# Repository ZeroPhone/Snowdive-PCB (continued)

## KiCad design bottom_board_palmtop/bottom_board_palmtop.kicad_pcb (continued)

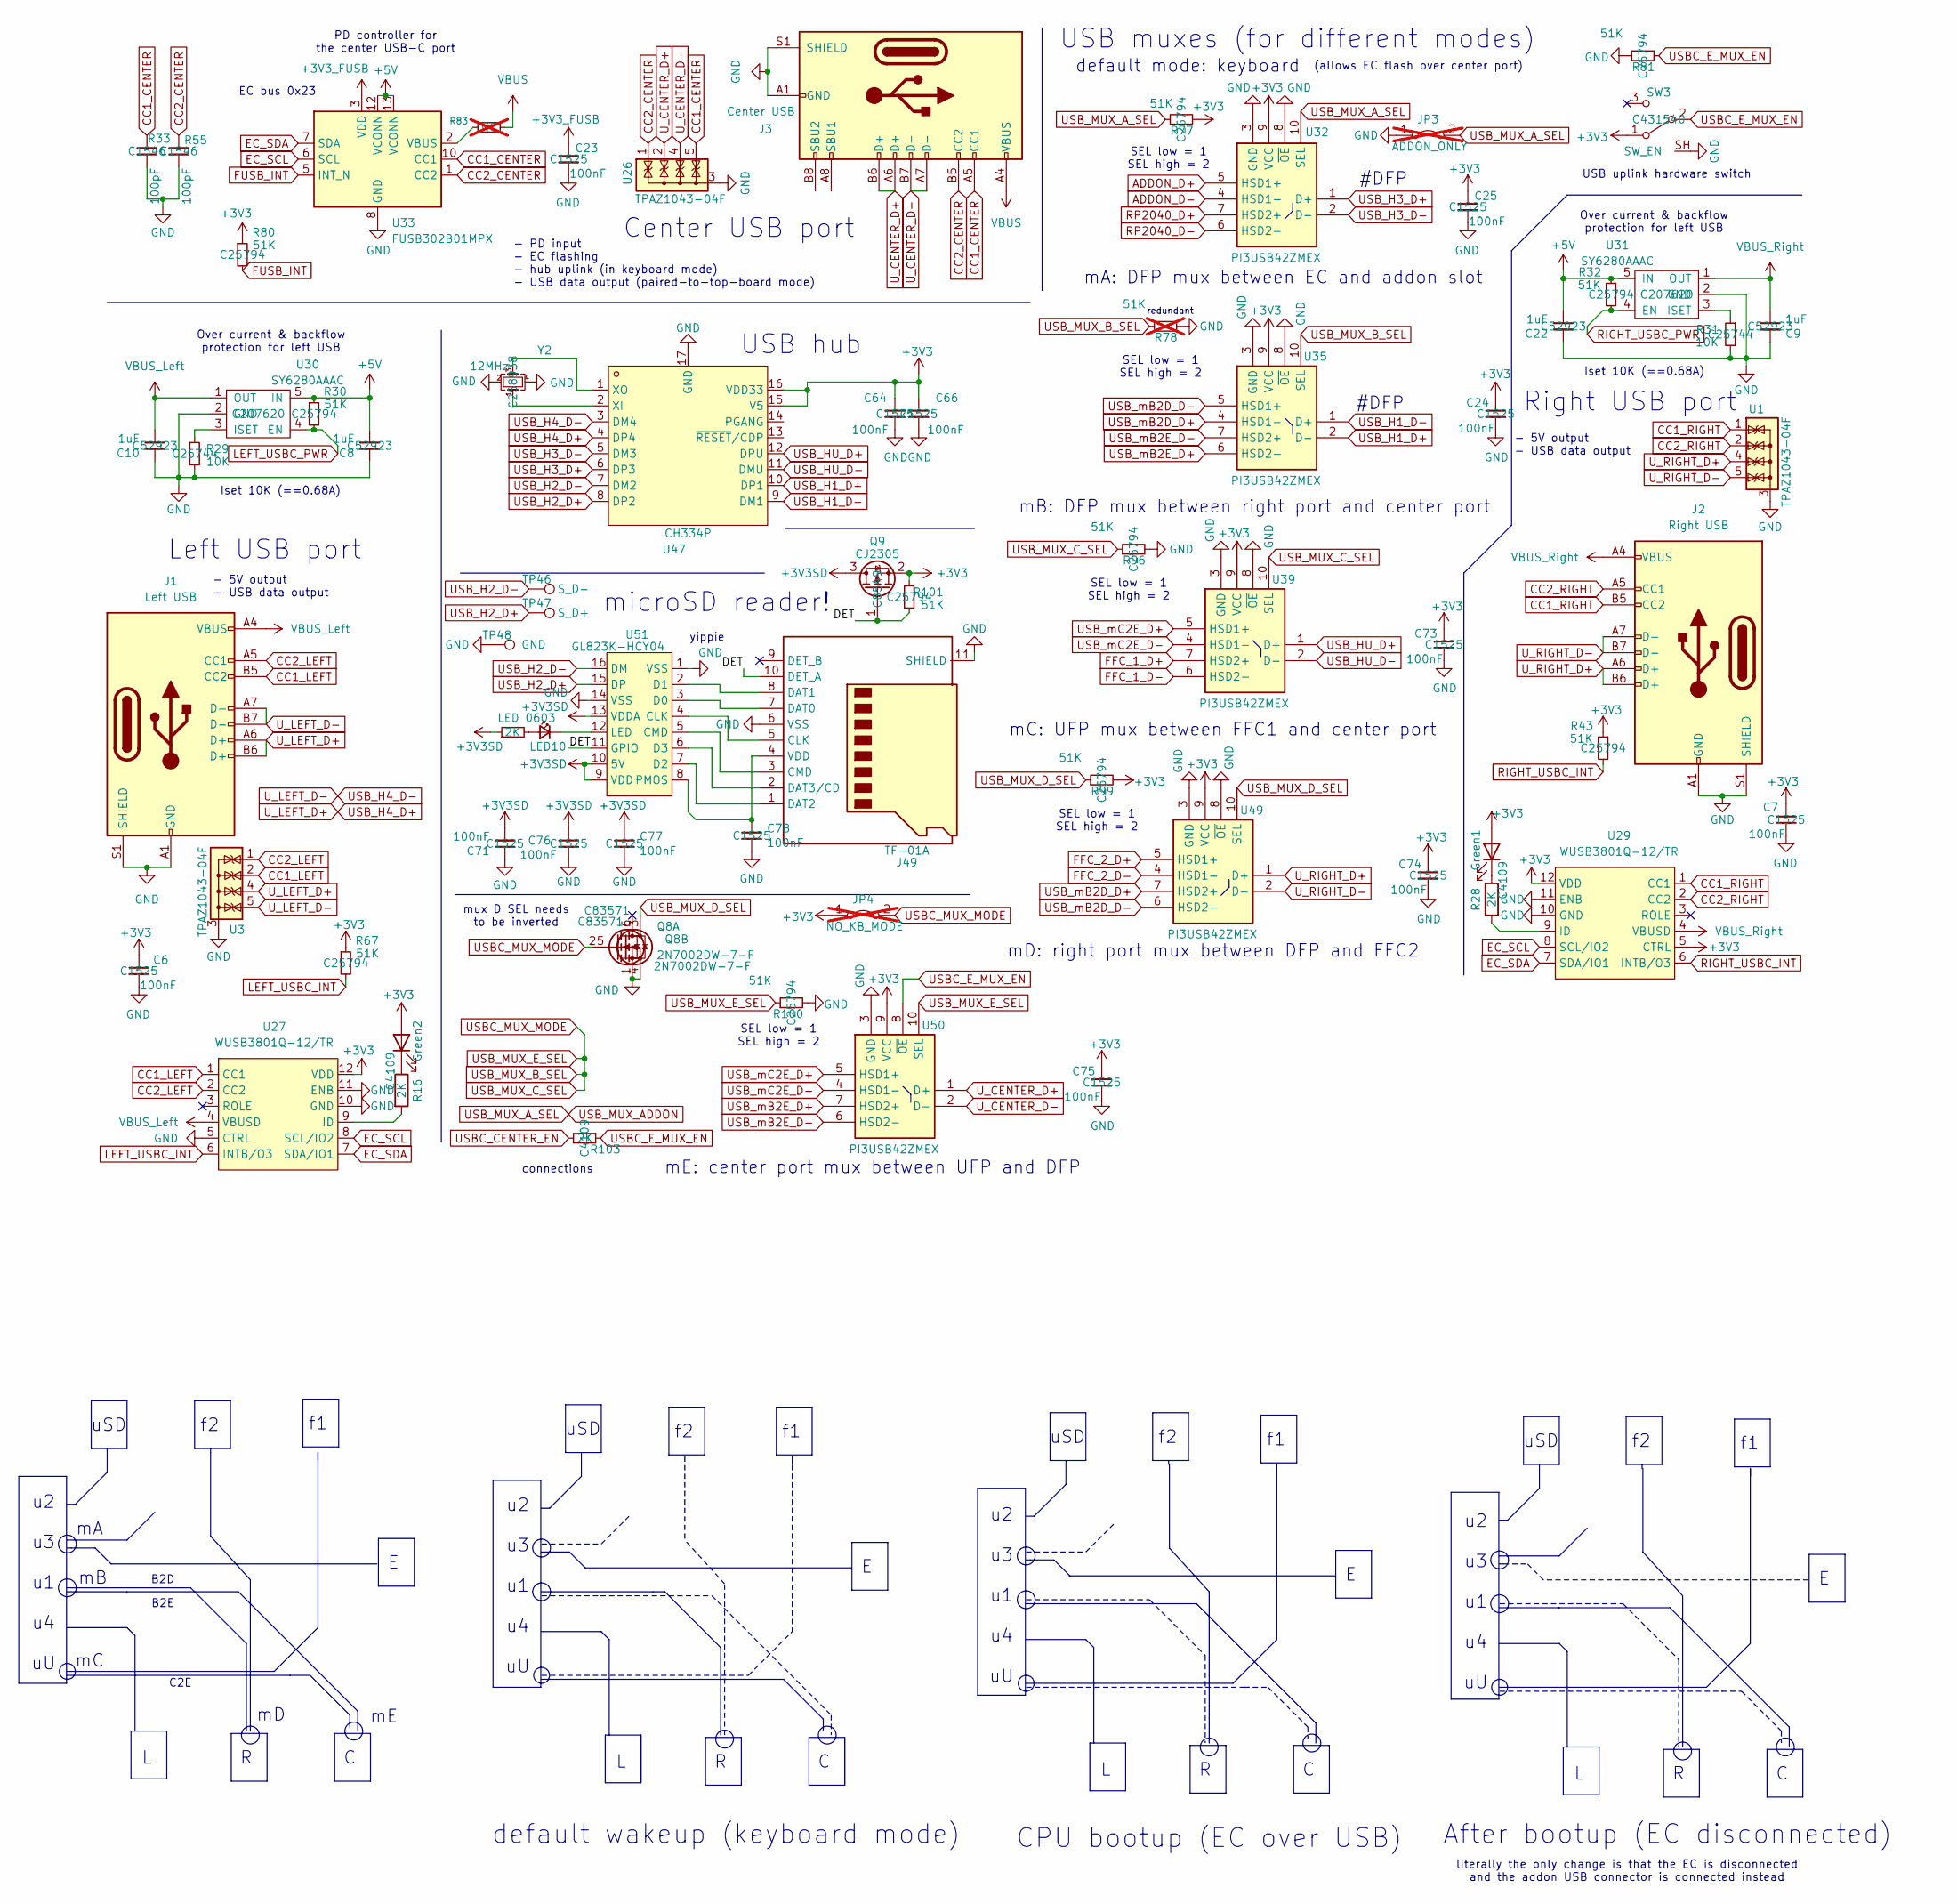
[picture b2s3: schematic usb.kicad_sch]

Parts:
C6, C7, C23, C24, C25, C64, C66, C71, C73, C74, C75, C76, C77, C78: 100nF; C_0402_1005Metric; LCSC Part C1525
C8, C9, C10, C22: 1uF; C_0402_1005Metric; LCSC Part C52923
Green1, Green2: LED 0603 Green; LED_0603_1608Metric
J1: Left USB; USB-C-TH_MC-710; LCSC Part C3039315
J2: Right USB; USB-C-TH_MC-710; LCSC Part C3039315
J3: Center USB; USB_C_Receptacle_HRO_TYPE-C-31-M-12; LCSC Part C165948
J49: TF-01A; microSD-Receptacle-SelfEject; LCSC Part C91145
JP3: ADDON_ONLY; SolderJumper-2_smol_Open; not fitted
JP4: NO_KB_MODE; SolderJumper-2_smol_Open; not fitted
LED10: LED 0603; LED_0603_1608Metric; LCSC Part C2977076
Q8: 2N7002DW-7-F; SOT-363_SC-70-6; LCSC Part C83571
Q9: CJ2305; SOT-23; LCSC Part C8549
R16, R28, R102, R103: 2K; R_0402_1005Metric; LCSC Part C4109
R29, R31: 10K; R_0402_1005Metric; LCSC Part C25744
R30, R32, R43, R67, R77, R80, R81, R96, R99, R100, R101: 51K; R_0402_1005Metric; LCSC Part C25794
R33, R55: 100pF; R_0402_1005Metric; LCSC Part C1546
R78: 51K; R_0402_1005Metric; LCSC Part C25794; not fitted
R83: NC; R_0402_1005Metric; not fitted
SW3: SW_EN; SW_SPDT_PCM12_SH; LCSC Part C431540
TP46: S_D-; TestPoint_Pad_0.6x0.6mm
TP47: S_D+; TestPoint_Pad_0.6x0.6mm
TP48: GND; TestPoint_Pad_0.6x0.6mm
U1, U3, U26: TPAZ1043-04F; USON-10_2.5x1.0mm_P0.5mm
U27, U29: WUSB3801Q-12/TR; X2QFN-12_L1.6-W1.6-P0.40-LS1.2; LCSC Part C2931342
U30, U31: SY6280AAAC; SOT-23-5; LCSC Part C207620
U32, U35, U39, U49, U50: PI3USB42ZMEX; QFN40P140X180X55-10N; Manufacturer_Part_Number FSUSB42UMX; Mouser Part Number 512-FSUSB42UMX
U33: FUSB302B01MPX; WQFN-14-1EP_2.5x2.5mm_P0.5mm_EP1.45x1.45mm
U47: CH334P; QFN-16-1EP_3x3mm_P0.5mm_EP1.7x1.7mm; LCSC Part C5373042
U51: GL823K-HCY04; SSOP-16_3.9x4.9mm_P0.635mm; LCSC Part C284879
Y2: 12MHz; Crystal_SMD_3225-4Pin_3.2x2.5mm; LCSC Part C258938

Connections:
+3V3: C6.1, C7.1, C24.1, C25.1, C64.1, C66.1, C73.1, C74.1, C75.1, Green1.2 (A), Green2.2 (A), JP4.1 (A), Q9.2 (S), R43.1, R67.1, R77.2, R80.1, R99.2, R101.1, SW3.1 (A), U27.12 (VDD), U29.5 (CTRL), U29.12 (VDD), U32.9 (VCC), U35.9 (VCC), U39.9 (VCC), U47.15 (V5), U47.16 (VDD33), U49.9 (VCC), U50.9 (VCC); also elsewhere on the board
+3V3SD: C71.2, C76.1, C77.1, Q9.3 (D), R102.1, U51.9 (VDD), U51.10 (5V), U51.13 (VDDA)
+3V3_FUSB: C23.1, U33.3 (VDD), U33.4 (VDD); also elsewhere on the board
+5V: C8.1, C22.1, R30.1, R32.1, U30.5 (IN), U31.5 (IN), U33.12 (VCONN), U33.13 (VCONN); also elsewhere on the board
/USB/DET: J49.10 (DET_A), Q9.1 (G), R101.2, U51.11 (GPIO)
ADDON_D+: U32.5 (HSD1+); also elsewhere on the board
ADDON_D-: U32.4 (HSD1-); also elsewhere on the board
CC1_CENTER: J3.A5 (CC1), R33.2, U26.5 (IO4), U26.6 (NC), U33.10 (CC1), U33.11 (CC1)
CC1_LEFT: J1.B5 (CC2), U3.2 (IO2), U3.9 (NC), U27.1 (CC1)
CC1_RIGHT: J2.B5 (CC2), U1.1 (IO1), U1.10 (NC), U29.1 (CC1)
CC2_CENTER: J3.B5 (CC2), R55.2, U26.1 (IO1), U26.10 (NC), U33.1 (CC2), U33.14 (CC2)
CC2_LEFT: J1.A5 (CC1), U3.1 (IO1), U3.10 (NC), U27.2 (CC2)
CC2_RIGHT: J2.A5 (CC1), U1.2 (IO2), U1.9 (NC), U29.2 (CC2)
EC_SCL: U27.8 (SCL/IO2), U29.8 (SCL/IO2), U33.6 (SCL); also elsewhere on the board
EC_SDA: U27.7 (SDA/IO1), U29.7 (SDA/IO1), U33.7 (SDA); also elsewhere on the board
FFC_1_D+: U39.7 (HSD2+); also elsewhere on the board
FFC_1_D-: U39.6 (HSD2-); also elsewhere on the board
FFC_2_D+: U49.5 (HSD1+); also elsewhere on the board
FFC_2_D-: U49.4 (HSD1-); also elsewhere on the board
FUSB_INT: R80.2, U33.5 (INT_N); also elsewhere on the board
GND: C6.2, C7.2, C8.2, C9.2, C10.2, C22.2, C23.2, C24.2, C25.2, C64.2, C66.2, C71.1, C73.2, C74.2, C75.2, C76.2, C77.2, C78.2, J1.A1 (GND), J1.A12 (GND), J1.B1 (GND), J1.B12 (GND), J1.S1 (SHIELD), J2.A1 (GND), J2.A12 (GND), J2.B1 (GND), J2.B12 (GND), J2.S1 (SHIELD), J3.A1 (GND), J3.A12 (GND), J3.B1 (GND), J3.B12 (GND), J3.S1 (SHIELD), J49.6 (VSS), J49.11 (SHIELD), JP3.1 (A), Q8.1 (S), Q8.4 (S), R29.2, R31.2, R33.1, R55.1, R78.2, R81.1, R96.2, R100.2, SW3.SH, TP48.1, U1.3 (G), U1.8 (G), U3.3 (G), U3.8 (G), U26.3 (G), U26.8 (G), U27.5 (CTRL), U27.10 (GND), U27.11 (ENB), U29.10 (GND), U29.11 (ENB), U30.2 (GND), U31.2 (GND), U32.3 (GND), U32.8 (~OE), U33.8 (GND), U33.9 (GND), U33.15 (GND), U35.3 (GND), U35.8 (~OE), U39.3 (GND), U39.8 (~OE), U47.17 (GND), U49.3 (GND), U49.8 (~OE), U50.3 (GND), U51.1 (VSS), U51.14 (VSS), Y2.2, Y2.4; also elsewhere on the board
LEFT_USBC_INT: R67.2, U27.6 (INTB/O3); also elsewhere on the board
LEFT_USBC_PWR: R30.2, U30.4 (EN); also elsewhere on the board
unnamed: Green1.1 (K), R28.1
unnamed: Green2.1 (K), R16.1
unnamed: J49.5 (CLK), U51.4 (CLK)
unnamed: J49.3 (CMD), U51.5 (CMD)
unnamed: J49.7 (DAT0), U51.3 (D0)
unnamed: J49.8 (DAT1), U51.2 (D1)
unnamed: J49.1 (DAT2), U51.7 (D2)
unnamed: J49.2 (DAT3/CD), U51.6 (D3)
unnamed: C78.1, J49.4 (VDD), U51.8 (PMOS)
unnamed: LED10.2 (A), R102.2
unnamed: LED10.1 (K), U51.12 (LED)
unnamed: R16.2, U27.9 (ID)
unnamed: R28.2, U29.9 (ID)
unnamed: R29.1, U30.3 (ISET)
unnamed: R31.1, U31.3 (ISET)
unnamed: R83.1, U33.2 (VBUS)
unnamed: U47.2 (XI), Y2.1
unnamed: U47.1 (XO), Y2.3
RIGHT_USBC_INT: R43.2, U29.6 (INTB/O3); also elsewhere on the board
RIGHT_USBC_PWR: R32.2, U31.4 (EN); also elsewhere on the board
RP2040_D+: U32.7 (HSD2+); also elsewhere on the board
RP2040_D-: U32.6 (HSD2-); also elsewhere on the board
USBC_CENTER_EN: R103.2; also elsewhere on the board
USBC_E_MUX_EN: R81.2, R103.1, SW3.2 (B), U50.8 (~OE)
USBC_MUX_MODE: JP4.2 (B), Q8.2 (G), Q8.5 (G), R78.1, R96.1, R100.1, U35.10 (SEL), U39.10 (SEL), U50.10 (SEL); also elsewhere on the board
USB_H1_D+: U35.2 (D-), U47.10 (DP1)
USB_H1_D-: U35.1 (D+), U47.9 (DM1)
USB_H2_D+: TP47.1, U47.8 (DP2), U51.15 (DP)
USB_H2_D-: TP46.1, U47.7 (DM2), U51.16 (DM)
USB_H3_D+: U32.1 (D+), U47.6 (DP3)
USB_H3_D-: U32.2 (D-), U47.5 (DM3)
USB_H4_D+: J1.A6 (D+), J1.B6 (D+), U3.4 (IO3), U3.7 (NC), U47.4 (DP4)
USB_H4_D-: J1.A7 (D-), J1.B7 (D-), U3.5 (IO4), U3.6 (NC), U47.3 (DM4)
USB_HU_D+: U39.1 (D+), U47.12 (DPU)
USB_HU_D-: U39.2 (D-), U47.11 (DMU)
USB_MUX_ADDON: JP3.2 (B), R77.1, U32.10 (SEL); also elsewhere on the board
USB_MUX_D_SEL: Q8.3 (D), R99.1, U49.10 (SEL)
USB_mB2D_D+: U35.4 (HSD1-), U49.7 (HSD2+)
USB_mB2D_D-: U35.5 (HSD1+), U49.6 (HSD2-)
USB_mB2E_D+: U35.6 (HSD2-), U50.7 (HSD2+)
USB_mB2E_D-: U35.7 (HSD2+), U50.6 (HSD2-)
USB_mC2E_D+: U39.5 (HSD1+), U50.5 (HSD1+)
USB_mC2E_D-: U39.4 (HSD1-), U50.4 (HSD1-)
U_CENTER_D+: J3.A6 (D+), J3.B6 (D+), U26.2 (IO2), U26.9 (NC), U50.1 (D+)
U_CENTER_D-: J3.A7 (D-), J3.B7 (D-), U26.4 (IO3), U26.7 (NC), U50.2 (D-)
U_RIGHT_D+: J2.A6 (D+), J2.B6 (D+), U1.4 (IO3), U1.7 (NC), U49.1 (D+)
U_RIGHT_D-: J2.A7 (D-), J2.B7 (D-), U1.5 (IO4), U1.6 (NC), U49.2 (D-)
VBUS: J3.A4 (VBUS), J3.A9 (VBUS), J3.B4 (VBUS), J3.B9 (VBUS), R83.2; also elsewhere on the board
VBUS_Left: C10.1, J1.A4 (VBUS), J1.A9 (VBUS), J1.B4 (VBUS), J1.B9 (VBUS), U27.4 (VBUSD), U30.1 (OUT)
VBUS_Right: C9.1, J2.A4 (VBUS), J2.A9 (VBUS), J2.B4 (VBUS), J2.B9 (VBUS), U29.4 (VBUSD), U31.1 (OUT)

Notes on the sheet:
default wakeup (keyboard mode)
Center USB port
yippie
literally the only change is that the EC is disconnected and the addon USB connector is connected instead
u2 u3 u1 u4 uU
SEL low = 1 SEL high = 2
C2E
Iset 10K (==0.68A)
default mode: keyboard
#DFP
uSD
- 5V output - USB data output
USB uplink hardware switch
microSD reader!
EC bus 0x23
USB muxes (for different modes)
mB: DFP mux between right port and center port
mC: UFP mux between FFC1 and center port
mD: right port mux between DFP and FFC2
B2E
Left USB port
mA: DFP mux between EC and addon slot
B2D
(allows EC flash over center port)
After bootup (EC disconnected)
Right USB port
USB hub
Over current & backflow protection for left USB
connections
CPU bootup (EC over USB)
PD controller for the center USB-C port
redundant
mE: center port mux between UFP and DFP
mux D SEL needs to be inverted
- PD input - EC flashing - hub uplink (in keyboard mode) - USB data output (paired-to-top-board mode)

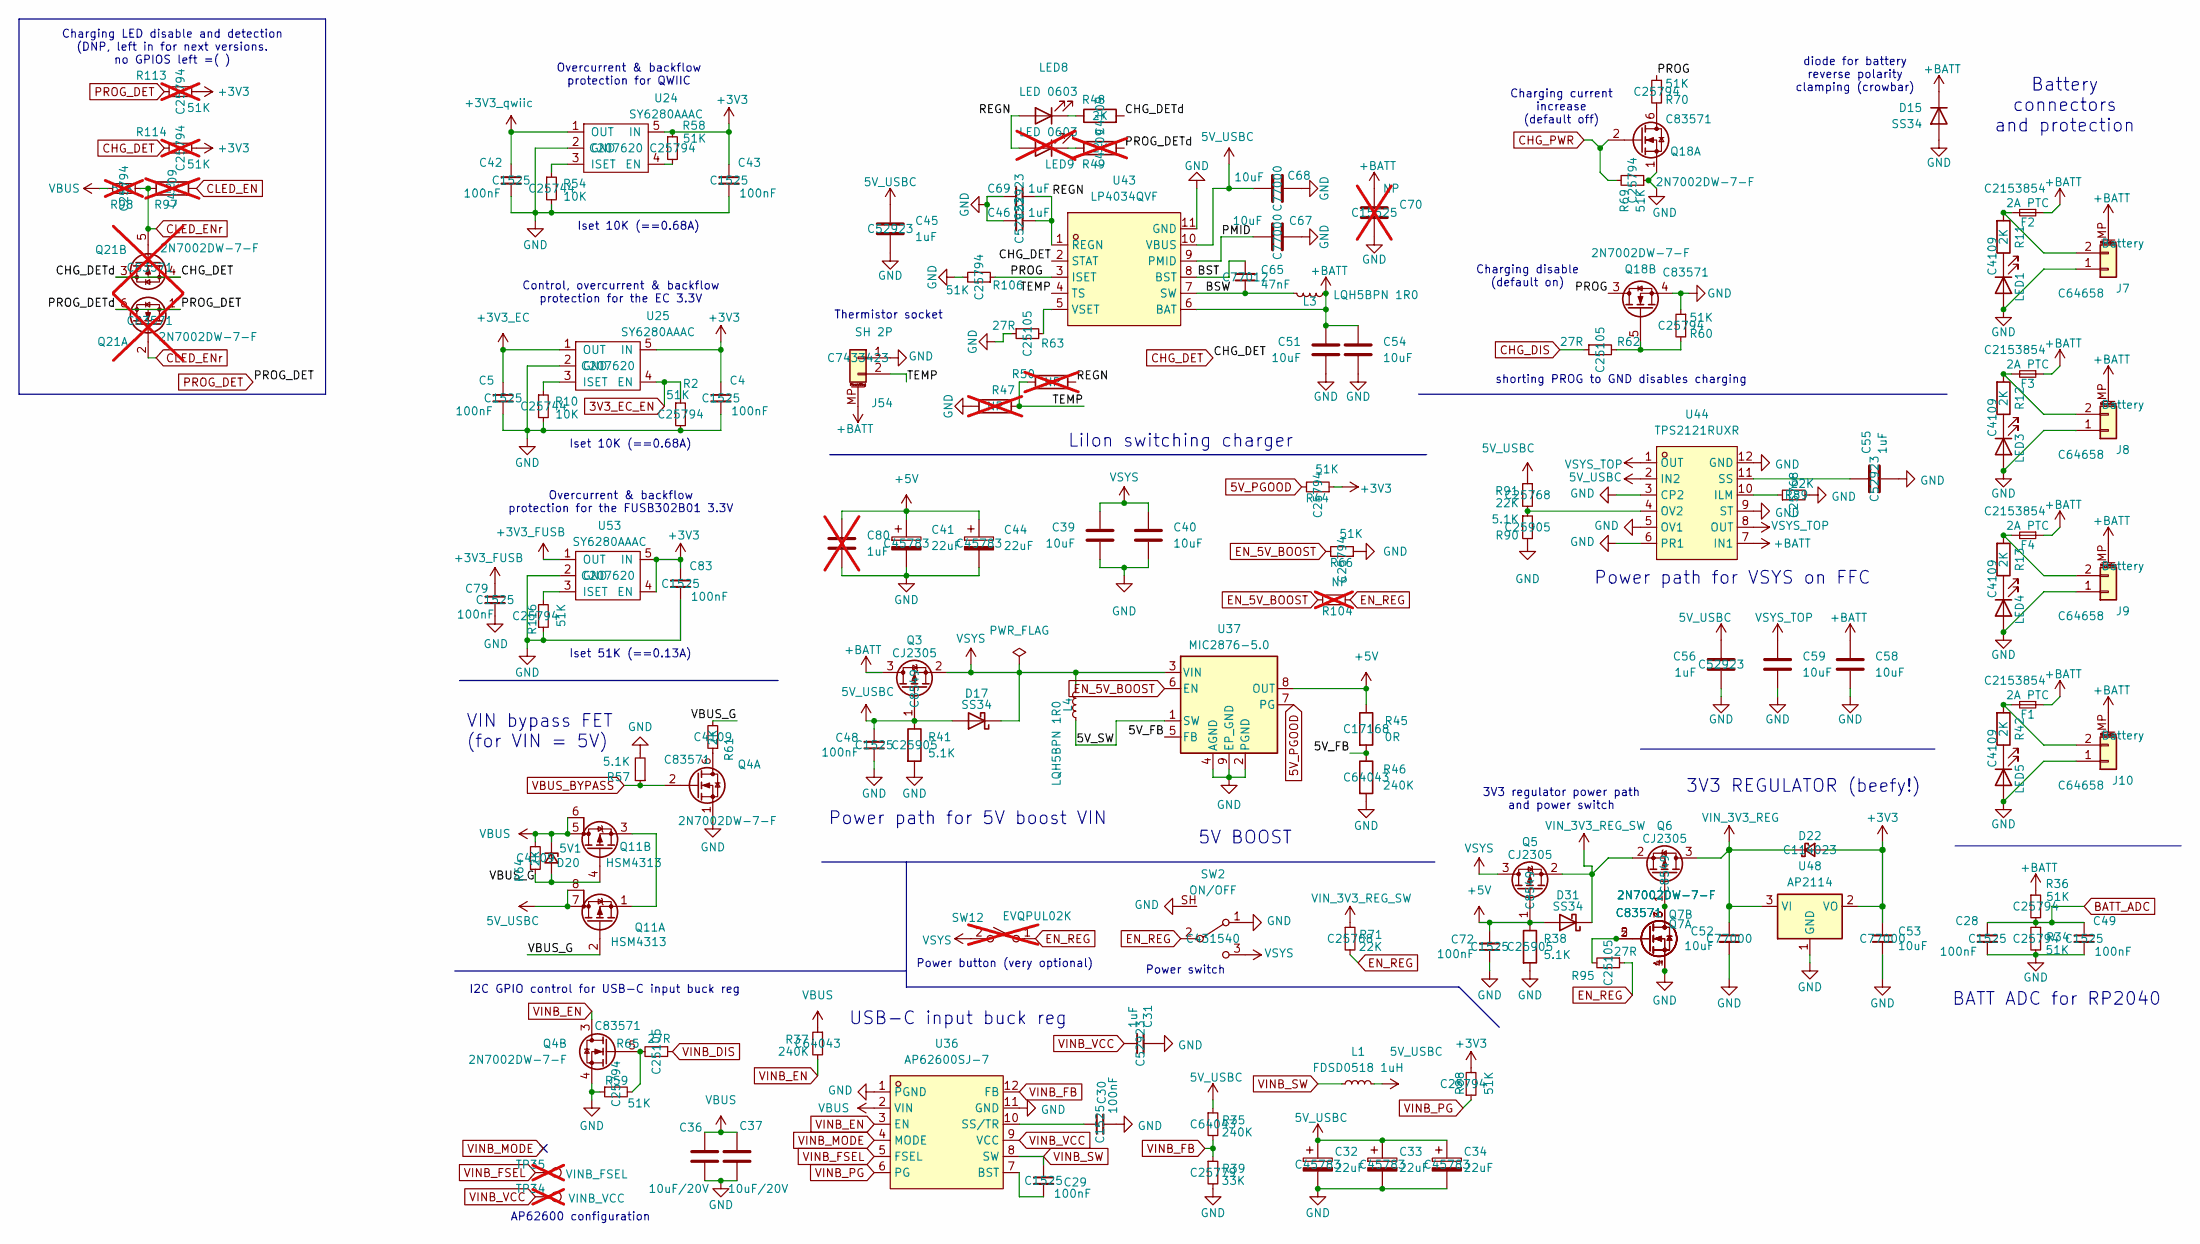
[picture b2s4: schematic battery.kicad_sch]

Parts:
C4, C5, C28, C29, C30, C42, C43, C48, C49, C72, C79, C83: 100nF; C_0402_1005Metric; LCSC Part C1525
C31, C45, C46, C55, C56, C69: 1uF; C_0402_1005Metric; LCSC Part C52923
C32, C33, C34, C41, C44: 22uF; C_0805_2012Metric_Pad1.18x1.45mm_HandSolder; LCSC Part C45783
C36, C37: 10uF/20V; C_0805_2012Metric_Pad1.18x1.45mm_HandSolder
C39, C40, C51, C54, C58, C59: 10uF; C_0805_2012Metric_Pad1.18x1.45mm_HandSolder
C52, C53, C67, C68: 10uF; C_0402_1005Metric; LCSC Part C77000
C65: 47nF; C_0402_1005Metric; LCSC Part C77012
C70: NP; C_0402_1005Metric; LCSC Part C15525; not fitted
C80: 1uF; C_0805_2012Metric_Pad1.18x1.45mm_HandSolder; not fitted
D15, D17, D31: SS34; D_SMA
D20: 5V1; D_0805_2012Metric
D22: D_Schottky_Small; D_SOD-323; LCSC Part C114023
F1, F2, F3, F4: 2A PTC; Fuse_1206_3216Metric; LCSC Part C2153854
J7, J8, J9, J10: Battery; JST_PH_B2B-PH-SM4-TB_1x02-1MP_P2.00mm_Vertical; LCSC Part C64658
J54: SH 2P; JST_SH_BM02B-SRSS-TB_1x02-1MP_P1.00mm_Vertical; LCSC Part C7433423
L1: FDSD0518 1uH; L_Murata_FDSD0518; LCSC Part C7511322
L3, L4: LQH5BPN 1R0; L_Murata_LQH5BPN; LCSC Part C337906
LED1, LED3, LED4, LED5: LED 0603 Orange; LED_0603_1608Metric; LCSC Part C965801
LED8: LED 0603; LED_0603_1608Metric; LCSC Part C965808
LED9: LED 0603; LED_0603_1608Metric; LCSC Part C965804; not fitted
Q3, Q5, Q6: CJ2305; SOT-23; LCSC Part C8549
Q4, Q7, Q18: 2N7002DW-7-F; SOT-363_SC-70-6; LCSC Part C83571
Q11: HSM4313; SO-8_3.9x4.9mm_P1.27mm
Q21: 2N7002DW-7-F; SOT-363_SC-70-6; LCSC Part C83571; not fitted
R2, R34, R36, R44, R58, R59, R60, R66, R69, R70, R88, R106, R116: 51K; R_0402_1005Metric; LCSC Part C25794
R10, R54: 10K; R_0402_1005Metric; LCSC Part C25744
R11, R12, R13, R42, R48, R61, R64: 2K; R_0402_1005Metric; LCSC Part C4109
R35, R37, R46: 240K; R_0402_1005Metric; LCSC Part C64043
R38, R41, R57, R90: 5.1K; R_0402_1005Metric; LCSC Part C25905
R39: 33K; R_0402_1005Metric; LCSC Part C25779
R45: 0R; R_0402_1005Metric; LCSC Part C17168
R47, R50: NP; R_0603_1608Metric; not fitted
R49, R97: 2K; R_0402_1005Metric; LCSC Part C4109; not fitted
R62, R63, R65, R95: 27R; R_0402_1005Metric; LCSC Part C25105
R71, R89, R91: 22K; R_0402_1005Metric; LCSC Part C25768
R98, R113, R114: 51K; R_0402_1005Metric; LCSC Part C25794; not fitted
R104: NP; R_0402_1005Metric; not fitted
SW2: ON/OFF; SW_SPDT_PCM12_SH; LCSC Part C431540
SW12: EVQPUL02K; Panasonic_EVQPUL_EVQPUC; not fitted
TP34: VINB_VCC; TestPoint_Pad_0.6x0.6mm; not fitted
TP35: VINB_FSEL; TestPoint_Pad_0.6x0.6mm; not fitted
U24, U25, U53: SY6280AAAC; SOT-23-5; LCSC Part C207620
U36: AP62600SJ-7; QFN-12_L3.0-W2.0-P0.50-TL_AP62600SJ-7; LCSC Part C4748917
U37: MIC2876-5.0; DFN-8-1EP_2x2mm_P0.5mm_EP0.6x1.2mm
U43: LP4034QVF; DFN-10-1EP_3x3mm_P0.5mm_EP1.58x2.35mm; LCSC Part C42460070
U44: TPS2121RUXR; VQFN-HR-12_L2.5-W2.0-P0.50-BL; LCSC Part C485916
U48: AP2114; SOT-223-3_TabPin2

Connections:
3V3_EC_EN: R2.1, U25.4 (EN); also elsewhere on the board
5V_PGOOD: R44.2, U37.7 (PG); also elsewhere on the board
5V_USBC: C32.1, C33.1, C34.1, C45.1, C48.2, C56.1, C68.1, D17.2 (A), L1.2, Q3.1 (G), Q11.7 (D), Q11.8 (G), R35.1, R41.1, R91.1, U43.10 (VBUS), U44.2 (IN2)
+3V3: C4.1, C43.1, C53.2, C83.1, D22.2 (A), R44.1, R58.1, R88.2, R113.2, R114.2, U24.5 (IN), U25.5 (IN), U48.2 (VO), U53.4 (EN), U53.5 (IN); also elsewhere on the board
+3V3_EC: C5.1, U25.1 (OUT); also elsewhere on the board
+3V3_FUSB: C79.1, U53.1 (OUT); also elsewhere on the board
+3V3_qwiic: C42.1, U24.1 (OUT); also elsewhere on the board
+5V: C41.1, C44.1, C72.2, C80.1, D31.2 (A), Q5.1 (G), R38.1, R45.1, U37.8 (OUT); also elsewhere on the board
+BATT: C51.2, C54.2, C58.2, C70.1, D15.1 (K), F1.1, F2.1, F3.1, F4.1, J7.MP (MountPin), J8.MP (MountPin), J9.MP (MountPin), J10.MP (MountPin), J54.MP (MountPin), L3.1, Q3.3 (D), R36.1, U43.6 (BAT), U44.7 (IN1); also elsewhere on the board
/Power/5V_FB: R45.2, R46.1, U37.5 (FB)
/Power/5V_SW: L4.1, U37.1 (SW)
/Power/BST: C65.2, U43.8 (BST)
/Power/BSW: C65.1, L3.2, U43.7 (SW)
/Power/PMID: C67.1, U43.9 (PMID)
/Power/PROG: Q18.3 (D), R70.1, R106.1, U43.3 (ISET)
/Power/REGN: C46.1, C69.1, LED8.2 (A), LED9.2 (A), R50.1, U43.1 (REGN)
/Power/TEMP: J54.2, R47.1, R50.2, U43.4 (TS)
/Power/VBUS_G: D20.2 (A), Q11.2 (G), Q11.4 (G), R61.2, R64.1
BATT_ADC: C28.1, C49.1, R34.1, R36.2; also elsewhere on the board
CHG_DET: Q21.3 (D), Q21.4 (S), R48.2, R114.1, U43.2 (STAT)
CHG_DIS: R62.1; also elsewhere on the board
CHG_PWR: Q18.2 (G), R69.2; also elsewhere on the board
EN_5V_BOOST: R66.2, R104.2, U37.6 (EN); also elsewhere on the board
EN_REG: R71.2, R95.1, R104.1, SW2.2 (B), SW12.1 (A)
GND: C4.2, C5.2, C28.2, C30.2, C31.2, C32.2, C33.2, C34.2, C36.1, C37.1, C39.1, C40.1, C41.2, C42.2, C43.2, C44.2, C45.2, C46.2, C48.1, C49.2, C51.1, C52.2, C53.1, C54.1, C55.2, C56.2, C58.1, C59.1, C67.2, C68.2, C69.2, C70.2, C72.1, C79.2, C80.2, C83.2, D15.2 (A), J7.1, J8.1, J9.1, J10.1, J54.1, LED1.2 (A), LED3.2 (A), LED4.2 (A), LED5.2 (A), Q4.1 (S), Q4.4 (S), Q7.1 (S), Q7.4 (S), Q18.1 (S), Q18.4 (S), R2.2, R10.2, R34.2, R38.2, R39.2, R41.2, R46.2, R47.2, R54.2, R57.2, R59.1, R60.1, R63.1, R66.1, R69.1, R89.2, R90.2, R106.2, R116.1, SW2.1 (A), SW2.SH, U24.2 (GND), U25.2 (GND), U36.1 (PGND), U36.11 (GND), U37.2 (PGND), U37.4 (AGND), U37.9 (EP_GND), U43.11 (GND), U44.3 (CP2), U44.5 (OV1), U44.6 (PR1), U44.9 (ST), U44.12 (GND), U48.1 (GND), U53.2 (GND); also elsewhere on the board
unnamed: F2.2, J7.2, R11.2
unnamed: F3.2, J8.2, R12.2
unnamed: F4.2, J9.2, R13.2
unnamed: F1.2, J10.2, R42.2
unnamed: LED1.1 (K), R11.1
unnamed: LED3.1 (K), R12.1
unnamed: LED4.1 (K), R13.1
unnamed: LED5.1 (K), R42.1
unnamed: LED8.1 (K), R48.1
unnamed: LED9.1 (K), R49.1
unnamed: Q4.6 (D), R61.1
unnamed: Q4.5 (G), R59.2, R65.2
unnamed: Q6.1 (G), Q7.3 (D), Q7.6 (D)
unnamed: Q7.2 (G), Q7.5 (G), R95.2
unnamed: Q11.1 (S), Q11.3 (S)
unnamed: Q18.6 (D), R70.2
unnamed: Q18.5 (G), R60.2, R62.2
unnamed: Q21.1 (S), Q21.6 (D), R49.2, R113.1
unnamed: Q21.2 (G), Q21.5 (G), R97.1, R98.2
unnamed: R58.2, U24.4 (EN)
unnamed: R54.1, U24.3 (ISET)
unnamed: R10.1, U25.3 (ISET)
unnamed: C29.2, U36.7 (BST)
unnamed: C30.1, U36.10 (SS/TR)
unnamed: R63.2, U43.5 (VSET)
unnamed: R89.1, U44.10 (ILM)
unnamed: R90.1, R91.2, U44.4 (OV2)
unnamed: C55.1, U44.11 (SS)
unnamed: R116.2, U53.3 (ISET)
VBUS: C36.2, C37.2, D20.1 (K), Q11.5 (D), Q11.6 (G), R37.1, R64.2, R98.1, U36.2 (VIN); also elsewhere on the board
VBUS_BYPASS: Q4.2 (G), R57.1; also elsewhere on the board
VINB_DIS: R65.1; also elsewhere on the board
VINB_EN: Q4.3 (D), R37.2, U36.3 (EN)
VINB_FB: R35.2, R39.1, U36.12 (FB)
VINB_FSEL: TP35.1, U36.5 (FSEL)
VINB_MODE: U36.4 (MODE)
VINB_PG: R88.1, U36.6 (PG); also elsewhere on the board
VINB_SW: C29.1, L1.1, U36.8 (SW)
VINB_VCC: C31.1, TP34.1, U36.9 (VCC)
VIN_3V3_REG: C52.1, D22.1 (K), Q6.3 (D), U48.3 (VI)
VIN_3V3_REG_SW: D31.1 (K), Q5.2 (S), Q6.2 (S), R71.1
VSYS: C39.2, C40.2, D17.1 (K), L4.2, Q3.2 (S), Q5.3 (D), SW2.3 (C), SW12.2 (B), U37.3 (VIN)
VSYS_TOP: C59.2, U44.1 (OUT), U44.8 (OUT); also elsewhere on the board

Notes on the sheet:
VIN bypass FET (for VIN = 5V)
5V BOOST
3V3 regulator power path and power switch
Power button (very optional)
Overcurrent & backflow protection for the FUSB302B01 3.3V
diode for battery reverse polarity clamping (crowbar)
I2C GPIO control for USB-C input buck reg
Iset 51K (==0.13A)
Overcurrent & backflow protection for QWIIC
Iset 10K (==0.68A)
LiIon switching charger
Control, overcurrent & backflow protection for the EC 3.3V
Battery connectors and protection
Thermistor socket
BATT ADC for RP2040
Power switch
3V3 REGULATOR (beefy!)
AP62600 configuration
Power path for 5V boost VIN
Charging current increase (default off)
Power path for VSYS on FFC
USB-C input buck reg
Charging disable (default on)
Charging LED disable and detection (DNP, left in for next versions. no GPIOS left =( )
shorting PROG to GND disables charging

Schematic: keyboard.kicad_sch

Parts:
D6, D7, D8, D9, D11, D12, D13, D14: KBLED; LTW-010DCG
Q1: 2N7002DW-7-F; SOT-363_SC-70-6; LCSC Part C83571; not fitted
R1: 27R; R_0402_1005Metric; LCSC Part C25105; not fitted
R3, R4, R5, R6, R7, R8, R9, R56: 270R; R_0402_1005Metric; LCSC Part C25104
R68, R72, R74, R75, R76, R79: 10K; R_0402_1005Metric; LCSC Part C25744
R94: 10K; R_0402_1005Metric; LCSC Part C25744; not fitted
R108: 27R; R_0402_1005Metric; LCSC Part C25105
SW1: KeebDeck_individual_keys; Keyboard_6R13C_IND
U2, U4, U7, U8, U9, U10, U11, U12, U13, U14, U15, U16, U17, U18, U19, U20: TPAZ1043-04F; USON-10_2.5x1.0mm_P0.5mm

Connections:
+3V3: R68.1, R72.1, R74.1, R75.1, R76.1, R79.1, R94.1; also elsewhere on the board
+5V: D6.2 (A), D7.2 (A), D8.2 (A), D9.2 (A), D11.2 (A), D12.2 (A), D13.2 (A), D14.2 (A); also elsewhere on the board
COL0: U2.3 (G), U2.8 (G), U4.3 (G), U4.8 (G); also elsewhere on the board
COL1: U7.3 (G), U7.8 (G), U8.3 (G), U8.8 (G); also elsewhere on the board
COL2: U9.3 (G), U9.8 (G), U10.3 (G), U10.8 (G); also elsewhere on the board
COL3: U11.3 (G), U11.8 (G), U12.3 (G), U12.8 (G); also elsewhere on the board
COL4: U13.3 (G), U13.8 (G), U14.3 (G), U14.8 (G); also elsewhere on the board
COL5: U15.3 (G), U15.8 (G), U16.3 (G), U16.8 (G); also elsewhere on the board
COL6: U17.3 (G), U17.8 (G), U18.3 (G), U18.8 (G); also elsewhere on the board
COL6_F: SW1.6f_c, U18.1 (IO1), U18.10 (NC)
COL6_G: SW1.6g_c, U18.2 (IO2), U18.9 (NC)
COL6_H: SW1.6h_c, U18.4 (IO3), U18.7 (NC)
COL6_I: SW1.6i_c, U18.5 (IO4), U18.6 (NC)
COL7: U19.3 (G), U19.8 (G), U20.3 (G), U20.8 (G); also elsewhere on the board
COL7_A: SW1.6a_c, U19.1 (IO1), U19.10 (NC)
COL7_B: SW1.6b_c, U19.2 (IO2), U19.9 (NC)
COL7_C: SW1.6c_c, U19.4 (IO3), U19.7 (NC)
COL7_D: SW1.6d_c, U19.5 (IO4), U19.6 (NC)
COL7_E: SW1.6e_c, U20.2 (IO2), U20.9 (NC)
COL7_F: SW1.1a_c, U20.4 (IO3), U20.7 (NC)
COL7_G: SW1.1h_c, U20.5 (IO4), U20.6 (NC)
COL7_H: U20.1 (IO1), U20.10 (NC); also elsewhere on the board
GND: Q1.1 (S), Q1.4 (S), SW1.1b_c, SW1.1c_c, SW1.1d_c, SW1.1e_c, SW1.1f_c, SW1.1g_c; also elsewhere on the board
KB_BL: R1.1, R108.2; also elsewhere on the board
KB_BL_D: Q1.3 (D), Q1.6 (D), R3.1, R4.1, R5.1, R6.1, R7.1, R8.1, R9.1, R56.1, R108.1
unnamed: D6.1 (K), R56.2
unnamed: D7.1 (K), R3.2
unnamed: D8.1 (K), R4.2
unnamed: D9.1 (K), R5.2
unnamed: D11.1 (K), R6.2
unnamed: D12.1 (K), R7.2
unnamed: D13.1 (K), R8.2
unnamed: D14.1 (K), R9.2
unnamed: Q1.2 (G), Q1.5 (G), R1.2, R94.2
unnamed: SW1.5a_c, U2.1 (IO1), U2.10 (NC)
unnamed: SW1.4a_c, U2.2 (IO2), U2.9 (NC)
unnamed: SW1.3a_c, U2.4 (IO3), U2.7 (NC)
unnamed: SW1.2a_c, U2.5 (IO4), U2.6 (NC)
unnamed: SW1.5b_c, U4.1 (IO1), U4.10 (NC)
unnamed: SW1.4b_c, U4.2 (IO2), U4.9 (NC)
unnamed: SW1.3b_c, U4.4 (IO3), U4.7 (NC)
unnamed: SW1.2b_c, U4.5 (IO4), U4.6 (NC)
unnamed: SW1.5c_c, U7.1 (IO1), U7.10 (NC)
unnamed: SW1.4c_c, U7.2 (IO2), U7.9 (NC)
unnamed: SW1.3c_c, U7.4 (IO3), U7.7 (NC)
unnamed: SW1.2c_c, U7.5 (IO4), U7.6 (NC)
unnamed: SW1.5d_c, U8.1 (IO1), U8.10 (NC)
unnamed: SW1.4d_c, U8.2 (IO2), U8.9 (NC)
unnamed: SW1.3d_c, U8.4 (IO3), U8.7 (NC)
unnamed: SW1.2d_c, U8.5 (IO4), U8.6 (NC)
unnamed: SW1.5e_c, U9.1 (IO1), U9.10 (NC)
unnamed: SW1.4e_c, U9.2 (IO2), U9.9 (NC)
unnamed: SW1.3e_c, U9.4 (IO3), U9.7 (NC)
unnamed: SW1.2e_c, U9.5 (IO4), U9.6 (NC)
unnamed: SW1.5f_c, U10.1 (IO1), U10.10 (NC)
unnamed: SW1.4f_c, U10.2 (IO2), U10.9 (NC)
unnamed: SW1.3f_c, U10.4 (IO3), U10.7 (NC)
unnamed: SW1.2f_c, U10.5 (IO4), U10.6 (NC)
unnamed: SW1.5g_c, U11.1 (IO1), U11.10 (NC)
unnamed: SW1.4g_c, U11.2 (IO2), U11.9 (NC)
unnamed: SW1.3g_c, U11.4 (IO3), U11.7 (NC)
unnamed: SW1.2g_c, U11.5 (IO4), U11.6 (NC)
unnamed: SW1.5h_c, U12.1 (IO1), U12.10 (NC)
unnamed: SW1.4h_c, U12.2 (IO2), U12.9 (NC)
unnamed: SW1.3h_c, U12.4 (IO3), U12.7 (NC)
unnamed: SW1.2h_c, U12.5 (IO4), U12.6 (NC)
unnamed: SW1.5j_c, U13.1 (IO1), U13.10 (NC)
unnamed: SW1.4j_c, U13.2 (IO2), U13.9 (NC)
unnamed: SW1.3j_c, U13.4 (IO3), U13.7 (NC)
unnamed: SW1.2j_c, U13.5 (IO4), U13.6 (NC)
unnamed: SW1.5i_c, U14.1 (IO1), U14.10 (NC)
unnamed: SW1.4i_c, U14.2 (IO2), U14.9 (NC)
unnamed: SW1.3i_c, U14.4 (IO3), U14.7 (NC)
unnamed: SW1.2i_c, U14.5 (IO4), U14.6 (NC)
unnamed: SW1.5l_c, U15.1 (IO1), U15.10 (NC)
unnamed: SW1.4l_c, U15.2 (IO2), U15.9 (NC)
unnamed: SW1.3l_c, U15.4 (IO3), U15.7 (NC)
unnamed: SW1.2l_c, U15.5 (IO4), U15.6 (NC)
unnamed: SW1.5k_c, U16.1 (IO1), U16.10 (NC)
unnamed: SW1.4k_c, U16.2 (IO2), U16.9 (NC)
unnamed: SW1.3k_c, U16.4 (IO3), U16.7 (NC)
unnamed: SW1.2k_c, U16.5 (IO4), U16.6 (NC)
unnamed: SW1.5m_c, U17.1 (IO1), U17.10 (NC)
unnamed: SW1.4m_c, U17.2 (IO2), U17.9 (NC)
unnamed: SW1.3m_c, U17.4 (IO3), U17.7 (NC)
unnamed: SW1.2m_c, U17.5 (IO4), U17.6 (NC)
ROW0: SW1.1a_o, SW1.2a_o, SW1.2c_o, SW1.2e_o, SW1.2g_o, SW1.2i_o, SW1.2k_o, SW1.2m_o; also elsewhere on the board
ROW1: SW1.3a_o, SW1.3c_o, SW1.3e_o, SW1.3g_o, SW1.3i_o, SW1.3k_o, SW1.3m_o, SW1.6d_o; also elsewhere on the board
ROW2: SW1.4a_o, SW1.4c_o, SW1.4e_o, SW1.4g_o, SW1.4i_o, SW1.4k_o, SW1.4m_o, SW1.6b_o; also elsewhere on the board
ROW3: SW1.5a_o, SW1.5c_o, SW1.5e_o, SW1.5g_o, SW1.5i_o, SW1.5k_o, SW1.5m_o; also elsewhere on the board
ROW4: SW1.1h_o, SW1.2b_o, SW1.2d_o, SW1.2f_o, SW1.2h_o, SW1.2j_o, SW1.2l_o, SW1.6f_o; also elsewhere on the board
ROW5: SW1.3b_o, SW1.3d_o, SW1.3f_o, SW1.3h_o, SW1.3j_o, SW1.3l_o, SW1.6c_o, SW1.6i_o; also elsewhere on the board
ROW6: SW1.4b_o, SW1.4d_o, SW1.4f_o, SW1.4h_o, SW1.4j_o, SW1.4l_o, SW1.6a_o, SW1.6h_o; also elsewhere on the board
ROW7: SW1.5b_o, SW1.5d_o, SW1.5f_o, SW1.5h_o, SW1.5j_o, SW1.5l_o, SW1.6e_o, SW1.6g_o; also elsewhere on the board
TOPB1: R79.2, SW1.1b_o; also elsewhere on the board
TOPB2: R76.2, SW1.1c_o; also elsewhere on the board
TOPB3: R75.2, SW1.1d_o; also elsewhere on the board
TOPB4: R74.2, SW1.1e_o; also elsewhere on the board
TOPB5: R72.2, SW1.1f_o; also elsewhere on the board
TOPB6: R68.2, SW1.1g_o; also elsewhere on the board

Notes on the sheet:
ROW3COL7H is used in Peripherals
ESD diodes repurposed as keyboard NKRO diodes
I'm sorry for this not being as readable =(
T̷̢̼̦̦̗̬͌̀̃̆̽̃̃͘͝H̶̗̱̻̏̓̃̊̈́̽͘͠͠Ȩ̴̖̪̤̥͇̟̩̒͒͐́̕͝ ̷̠̙͌͂͗̓K̶̤̪̥̥̜̪͉̔͑͑̿́͗̄̉̃͠E̵̛̦̞͓͉̝̱̫̞͕̮̽̎̈́̆͜͝Y̷̧̜͉̝̜͙̞̟͔̭̾̾̆̓̈͛͊̏͜B̵̨͎͉̈́̓̉Ơ̷̜̥̠̥̥͎̞̩͉̝̞̒̀̔͒̅͝͝Ḁ̵̹̉̍͆̈́Ŕ̷̠̥̱̻̮̌̇͊̈͝D̴̨̫̖̙̲̼̓͜
Keyboard backlight LEDs
Button pullups for I2C GPIO-connected buttons
